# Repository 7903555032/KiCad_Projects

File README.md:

# KiCad_Projects
This repo have my some kicad project files

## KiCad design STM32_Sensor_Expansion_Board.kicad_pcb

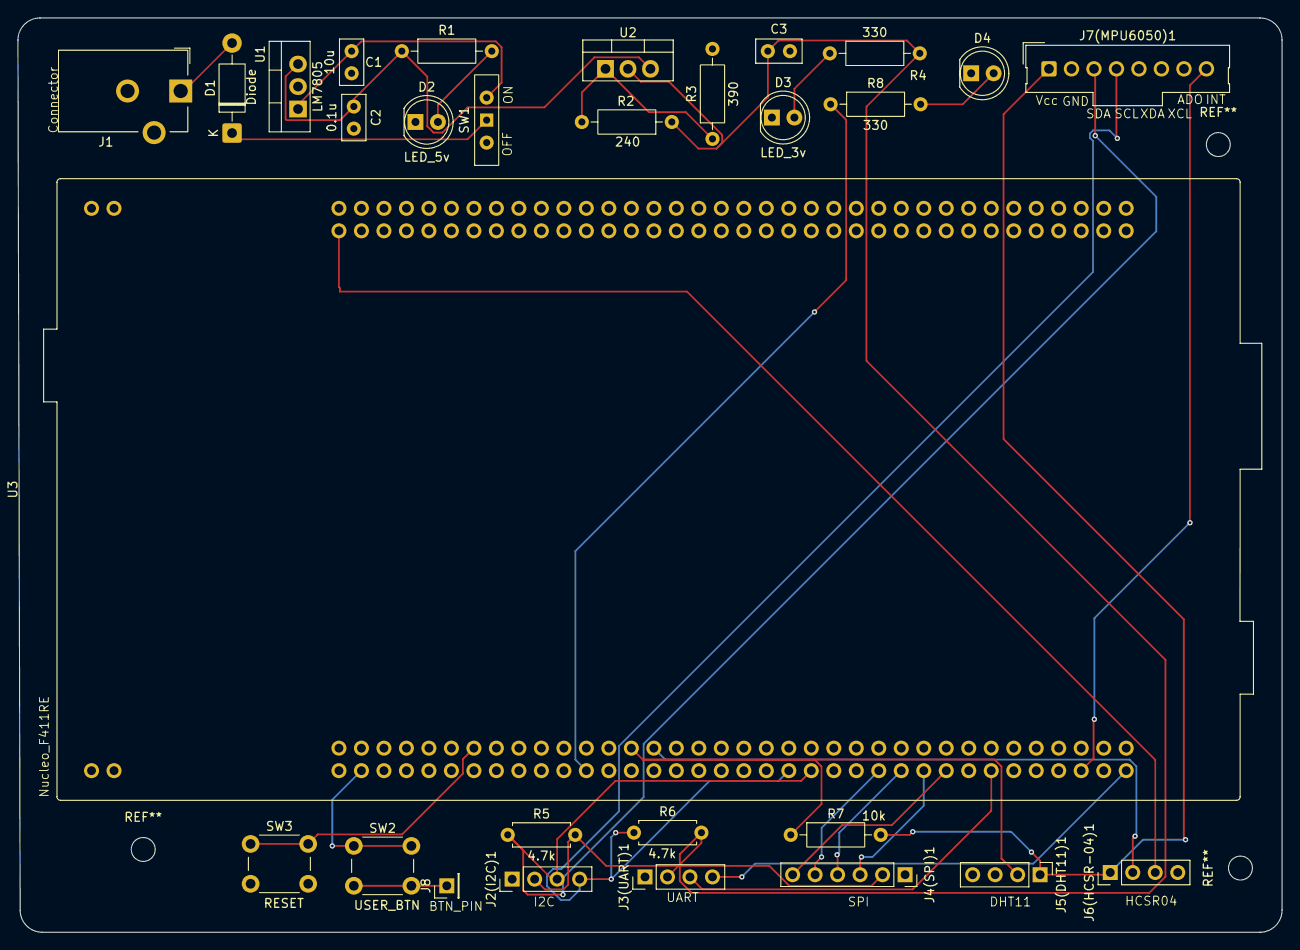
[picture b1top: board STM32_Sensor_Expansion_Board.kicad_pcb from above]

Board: 2 copper layers, 142.8 x 103.2 mm, 29 parts (0 on the bottom side), 27 nets.

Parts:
C1: 10u; C_Disc_D5.0mm_W2.5mm_P2.50mm
C2: 0.1u; C_Disc_D5.0mm_W2.5mm_P2.50mm
C3: C; C_Disc_D5.0mm_W2.5mm_P2.50mm
D1: Diode; D_DO-41_SOD81_P10.16mm_Horizontal
D2: LED_5v; LED_D5.0mm
D3: LED_3v; LED_D5.0mm
D4: LED_Power; LED_D5.0mm
J1: Barrel_Jack_Switch; BarrelJack_CUI_PJ-102AH_Horizontal
J2(I2C)1, J3(UART)1, J5(DHT11)1, J6(HCSR-04)1: Conn_01x04_Pin; PinHeader_1x04_P2.54mm_Vertical
J4(SPI)1: Conn_01x06_Pin; PinSocket_1x06_P2.54mm_Vertical
J7(MPU6050)1: Conn_01x08_Pin; Molex_SL_171971-0008_1x08_P2.54mm_Vertical
J8: Conn_01x01_Pin; PinHeader_1x01_P2.54mm_Vertical
R1, R4, R8: 330; R_Axial_DIN0207_L6.3mm_D2.5mm_P10.16mm_Horizontal
R2: 240; R_Axial_DIN0207_L6.3mm_D2.5mm_P10.16mm_Horizontal
R3: 390; R_Axial_DIN0207_L6.3mm_D2.5mm_P10.16mm_Horizontal
R5, R6: 4.7k; R_Axial_DIN0207_L6.3mm_D2.5mm_P7.62mm_Horizontal
R7: 10k; R_Axial_DIN0207_L6.3mm_D2.5mm_P10.16mm_Horizontal
SW1: SW_SPDT_312; SW_Slide-03_Wuerth-WS-SLTV_10x2.5x6.4_P2.54mm
SW2: USER_BTN; SW_PUSH_6mm
SW3: RESET; SW_PUSH_6mm
U1: LM7805; TO-220-3_Vertical
U2: LM317; TO-220-3_Vertical
U3: NUCLEO64-F411RE; ST_Morpho_Connector_144_STLink

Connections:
/3v: C3.1, J2(I2C)1.2, J3(UART)1.2, J4(SPI)1.2, R2.1, R4.1, R5.2, R6.2, U2.2 (VO)
/5v: C2.1, R1.1, U1.3 (VO), U2.3 (VI)
/12v: C1.1, SW1.3 (A), U1.1 (VI)
/CS: J4(SPI)1.6, U3.55 (PB6)
/DHT11_DATA: J5(DHT11)1.2, R7.1, U3.28 (PA0)
/HC-TRIG: J6(HCSR-04)1.2, U3.30 (PA1)
/HC_ECHO: J6(HCSR-04)1.3, U3.73 (STLINK_UART_TX/PA2)
/INT: J7(MPU6050)1.8, U3.67 (PB5)
/LED_3v: D3.2 (A), R4.2
/LED_5v: D2.2 (A), R1.2
/MISO: J4(SPI)1.4, U3.51 (PA6)
/MOSI: J4(SPI)1.3, U3.53 (PA7)
/NRST: SW3.1, U3.14 (~RESET)
/PWR_Input: D1.1 (K), SW1.1 (B)
/RX: J3(UART)1.4, U3.71 (PA10)
/SCK: J4(SPI)1.5, U3.49 (PA5)
/SCL: J2(I2C)1.4, J7(MPU6050)1.4, R6.1, U3.41 (PB8)
/SDA: J2(I2C)1.3, J7(MPU6050)1.3, R5.1, U3.43 (PB9)
/TX: J3(UART)1.3, U3.59 (PA9)
/USER_BTN: SW2.1, U3.3 (PC12)
/USER_LED: R8.1, U3.23 (PC13)
/VCC: J5(DHT11)1.1, J6(HCSR-04)1.1, J7(MPU6050)1.1, R7.2
GND: C1.2, C2.2, C3.2, D2.1 (K), D3.1 (K), D4.1 (K), J1.2, J1.3, J2(I2C)1.1, J3(UART)1.1, J4(SPI)1.1, J5(DHT11)1.4, J6(HCSR-04)1.4, J7(MPU6050)1.2, R3.2, SW3.2, U1.2 (GND), U3.8 (GND), U3.19 (GND), U3.20 (GND), U3.22 (GND), U3.47 (GND), U3.58 (GND), U3.77 (GND), U3.78 (GND), U3.79 (GND), U3.80 (GND)
unnamed: D1.2 (A), J1.1
unnamed: D4.2 (A), R8.2
unnamed: J8.1 (Pin_1_1), SW2.2
unnamed: R2.2, R3.1, U2.1 (ADJ)

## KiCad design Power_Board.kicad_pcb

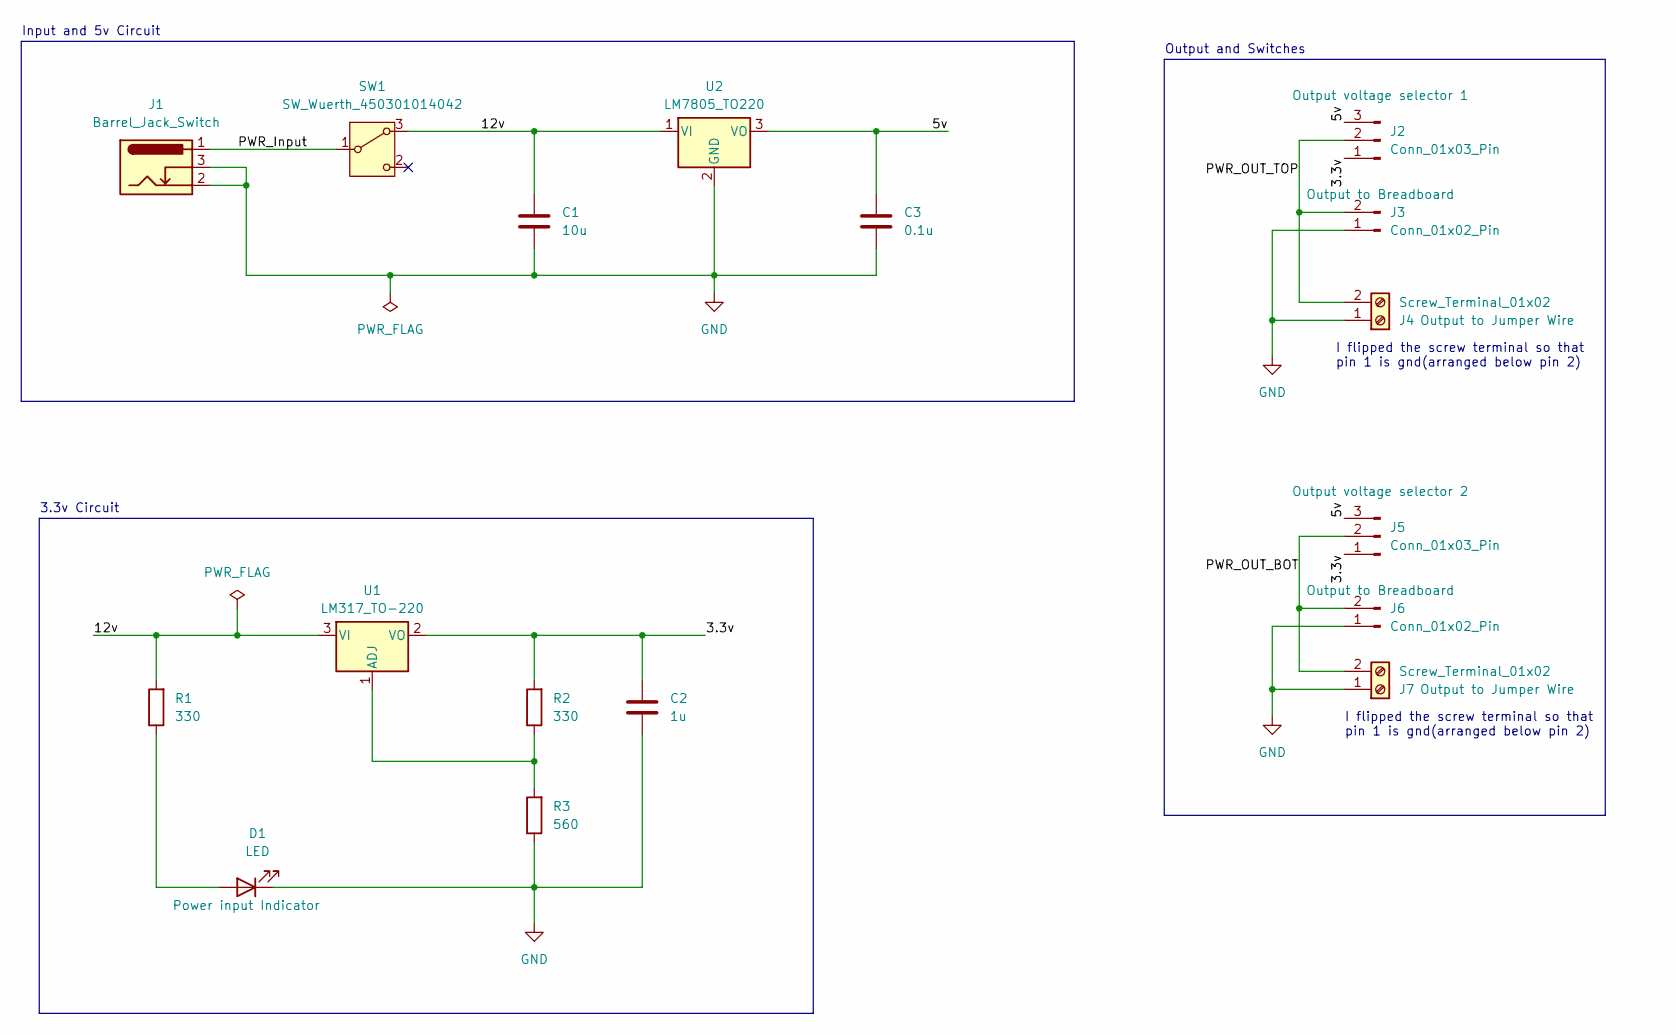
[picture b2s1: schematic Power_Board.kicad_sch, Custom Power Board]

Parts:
C1: 10u; C_Disc_D3.0mm_W1.6mm_P2.50mm
C2: 1u; C_Disc_D3.0mm_W1.6mm_P2.50mm
C3: 0.1u; C_Disc_D3.0mm_W1.6mm_P2.50mm
D1: LED; LED_D5.0mm
J1: Barrel_Jack_Switch; BarrelJack_Horizontal
J2, J5: Conn_01x03_Pin; PinHeader_1x03_P2.54mm_Vertical
J3, J6: Conn_01x02_Pin; PinHeader_1x02_P2.54mm_Vertical
J4, J7: Screw_Terminal_01x02; TerminalBlock_Xinya_XY308-2.54-2P_1x02_P2.54mm_Horizontal
R1, R2: 330; R_Axial_DIN0204_L3.6mm_D1.6mm_P7.62mm_Horizontal
R3: 560; R_Axial_DIN0204_L3.6mm_D1.6mm_P7.62mm_Horizontal
SW1: SW_Wuerth_450301014042; SW_Slide-03_Wuerth-WS-SLTV_10x2.5x6.4_P2.54mm
U1: LM317_TO-220; TO-220-3_Vertical
U2: LM7805_TO220; TO-220-3_Vertical

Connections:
/3.3v: C2.1, J2.1, J5.1, R2.2, U1.2 (VO)
/5v: C3.1, J2.3, J5.3, U2.3 (VO)
/12v: C1.1, R1.2, SW1.3 (A), U1.3 (VI), U2.1 (VI)
/PWR_Input: J1.1, SW1.1 (B)
/PWR_OUT_BOT: J5.2, J6.2, J7.2
/PWR_OUT_TOP: J2.2, J3.2, J4.2
GND: C1.2, C2.2, C3.2, D1.1 (K), J1.2, J1.3, J3.1, J4.1, J6.1, J7.1, R3.1, U2.2 (GND)
unnamed: D1.2 (A), R1.1
unnamed: R2.1, R3.2, U1.1 (ADJ)

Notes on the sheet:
3.3v Circuit
I flipped the screw terminal so that pin 1 is gnd(arranged below pin 2)
Output and Switches
Input and 5v Circuit

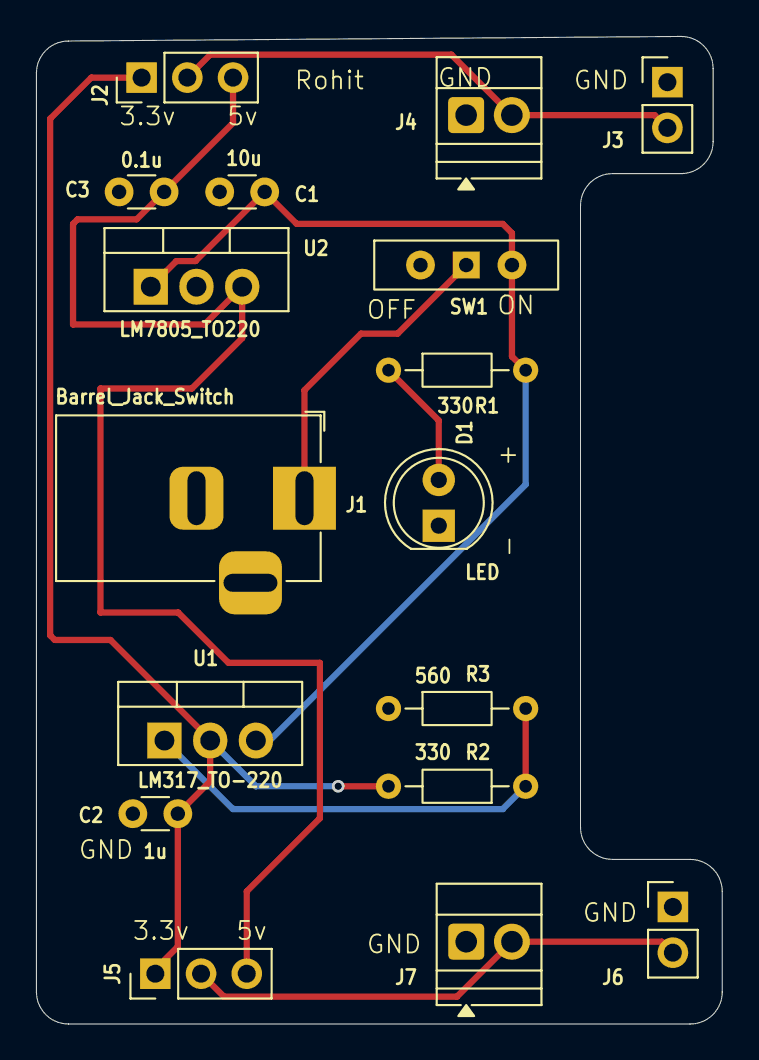
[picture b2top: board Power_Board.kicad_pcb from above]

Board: 2 copper layers, 38.1 x 54.9 mm, 17 parts (0 on the bottom side), 9 nets.

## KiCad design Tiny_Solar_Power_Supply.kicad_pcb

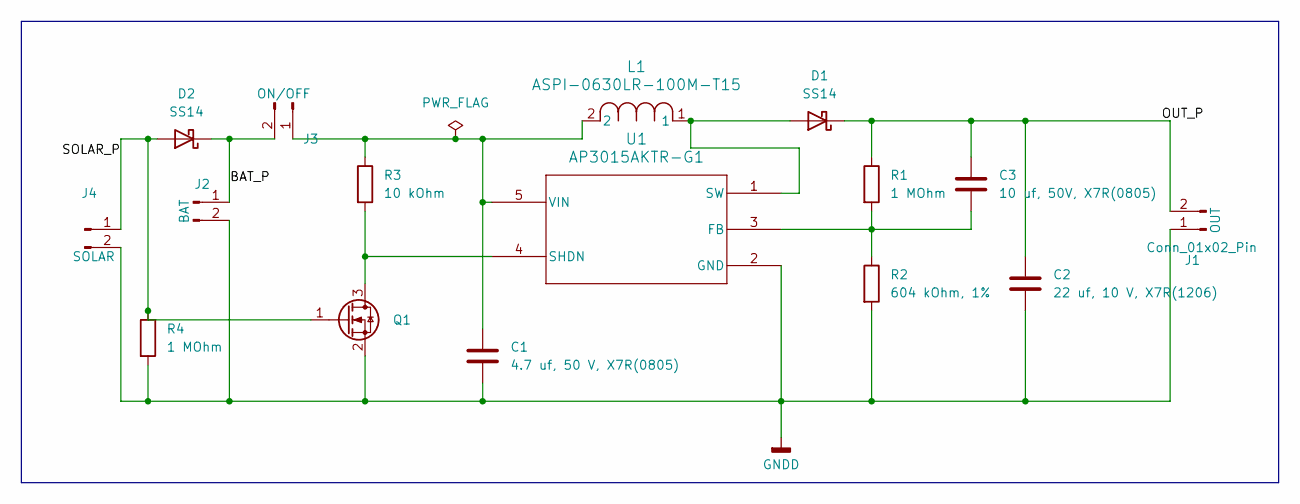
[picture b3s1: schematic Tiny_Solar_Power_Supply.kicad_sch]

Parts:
C1: 4.7 uf, 50 V, X7R(0805); C_0805_2012Metric
C2: 22 uf, 10 V, X7R(1206); C_1206_3216Metric
C3: 10 uf, 50V, X7R(0805); D_0805_2012Metric
D1, D2: SS14; D_SMA
J1, J2, J3: Conn_01x02_Pin; PinHeader_1x02_P2.54mm_Vertical
J4: Conn_01x02_Pin; PinHeader_1x02_P2.54mm_Horizontal
L1: ASPI-0630LR-100M-T15; IND_ASPI-0630LR_ABR
Q1: 2N7002; SOT-23
R1, R4: 1 MOhm; R_0805_2012Metric
R2: 604 kOhm, 1%; R_0805_2012Metric
R3: 10 kOhm; R_0805_2012Metric
U1: AP3015AKTR-G1; SOT23-5_1P55X2P9_DIO

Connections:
/BAT_P: D2.1 (K), J2.1, J3.2
/OUT_P: C2.1, C3.1, D1.1 (K), J1.2, R1.1
/SOLAR_P: D2.2 (A), J4.1, Q1.1 (G), R4.1
GNDD: C1.2, C2.2, J1.1, J2.2, J4.2, Q1.2 (S), R2.2, R4.2, U1.2 (GND)
unnamed: D1.2 (A), L1.1, U1.1 (SW)
unnamed: C1.1, J3.1, L1.2, R3.1, U1.5 (VIN)
unnamed: Q1.3 (D), R3.2, U1.4 (SHDN)
unnamed: C3.2, R1.2, R2.1, U1.3 (FB)

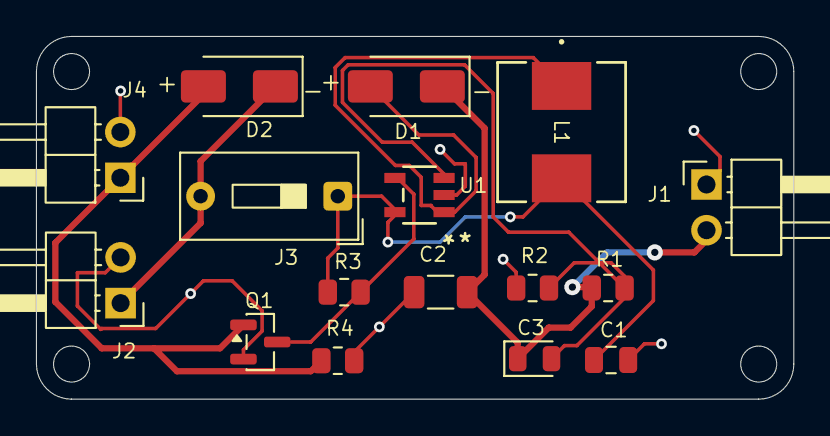
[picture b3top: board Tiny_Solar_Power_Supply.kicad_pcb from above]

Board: 2 copper layers, 42.1 x 20.2 mm, 16 parts (0 on the bottom side), 8 nets.
